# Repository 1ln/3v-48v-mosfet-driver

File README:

Fieldeffector pcb

Hardware Design: 

Dan Olson 
Copyright 2019

This board is currently is testing phase, use at your own risk.

This is a board designed to control n-channel power mosfets from a 3.3v microcontrollers using the mcp1416. 

Typical uses:

Solenoid control.

Features:

Four channels in two port configuration for mcu boards that have the same pinout.
Ability to also use 5v logic.

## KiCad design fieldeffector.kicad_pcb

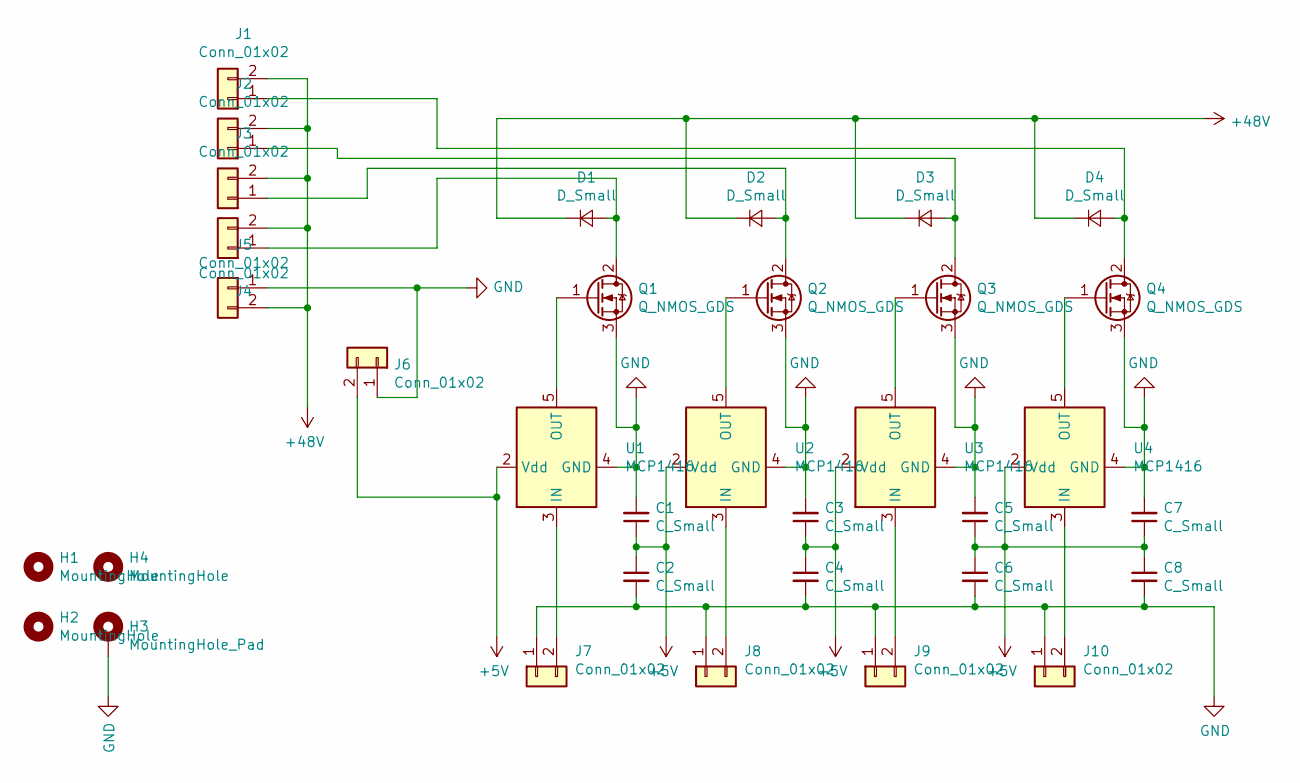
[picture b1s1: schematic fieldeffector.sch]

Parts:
C1, C2, C3, C4, C5, C6, C7, C8: C_Small; C_0603_1608Metric
D1, D2, D3, D4: D_Small; D_SMB
H1, H2, H4: MountingHole; MountingHole_3.2mm_M3
H3: MountingHole_Pad; MountingHole_3.2mm_M3_Pad_Via
J1, J2, J3, J4, J5: Conn_01x02; TerminalBlock_Phoenix_PT-1,5-2-3.5-H_1x02_P3.50mm_Horizontal
J6, J7, J8, J9, J10: Conn_01x02; PinHeader_1x02_P2.54mm_Vertical
Q1, Q2, Q3, Q4: Q_NMOS_GDS; TO-263-2
U1, U2, U3, U4: MCP1416; SOT-23-5

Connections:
+5V: C1.1, C2.1, C3.1, C4.1, C5.1, C6.1, C7.1, C8.1, J6.2, U1.2 (Vdd), U2.2 (Vdd), U3.2 (Vdd), U4.2 (Vdd)
+48V: D1.1 (K), D2.1 (K), D3.1 (K), D4.1 (K), J1.2, J2.2, J3.2, J4.2, J5.2
GND: C1.2, C2.2, C3.2, C4.2, C5.2, C6.2, C7.2, C8.2, H3.1, J5.1, J6.1, J7.1, J8.1, J9.1, J10.1, Q1.3 (S), Q2.3 (S), Q3.3 (S), Q4.3 (S), U1.4 (GND), U2.4 (GND), U3.4 (GND), U4.4 (GND)
unnamed: D1.2 (A), J4.1, Q1.2 (D)
unnamed: D2.2 (A), J3.1, Q2.2 (D)
unnamed: D3.2 (A), J2.1, Q3.2 (D)
unnamed: D4.2 (A), J1.1, Q4.2 (D)
unnamed: J7.2, U1.3 (IN)
unnamed: J8.2, U2.3 (IN)
unnamed: J9.2, U3.3 (IN)
unnamed: J10.2, U4.3 (IN)
unnamed: Q1.1 (G), U1.5 (OUT)
unnamed: Q2.1 (G), U2.5 (OUT)
unnamed: Q3.1 (G), U3.5 (OUT)
unnamed: Q4.1 (G), U4.5 (OUT)

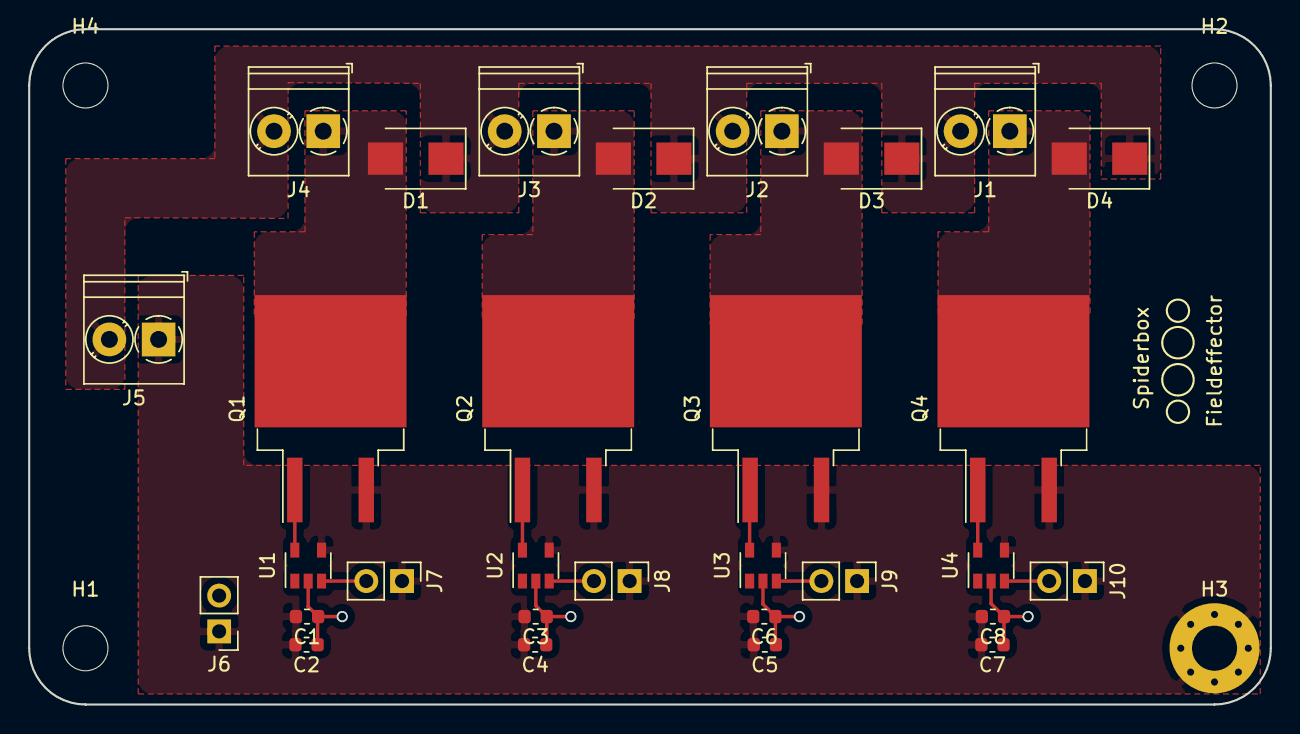
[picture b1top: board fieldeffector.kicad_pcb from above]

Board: 2 copper layers, 88.2 x 48.0 mm, 34 parts (0 on the bottom side), 15 nets.

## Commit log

2019-04-05 add netlist
2019-04-10 update layout
2019-04-12 add 3d image
2019-04-13 add gerber
2019-04-14 add system ground
2019-05-12 fixed diode pads
2019-05-13 add README
